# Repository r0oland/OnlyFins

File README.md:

# OnlyFins

ESPHome based smart radiator fans with temperature guided PWM Fan control. 

Ìnstall uv:
`winget install uv`

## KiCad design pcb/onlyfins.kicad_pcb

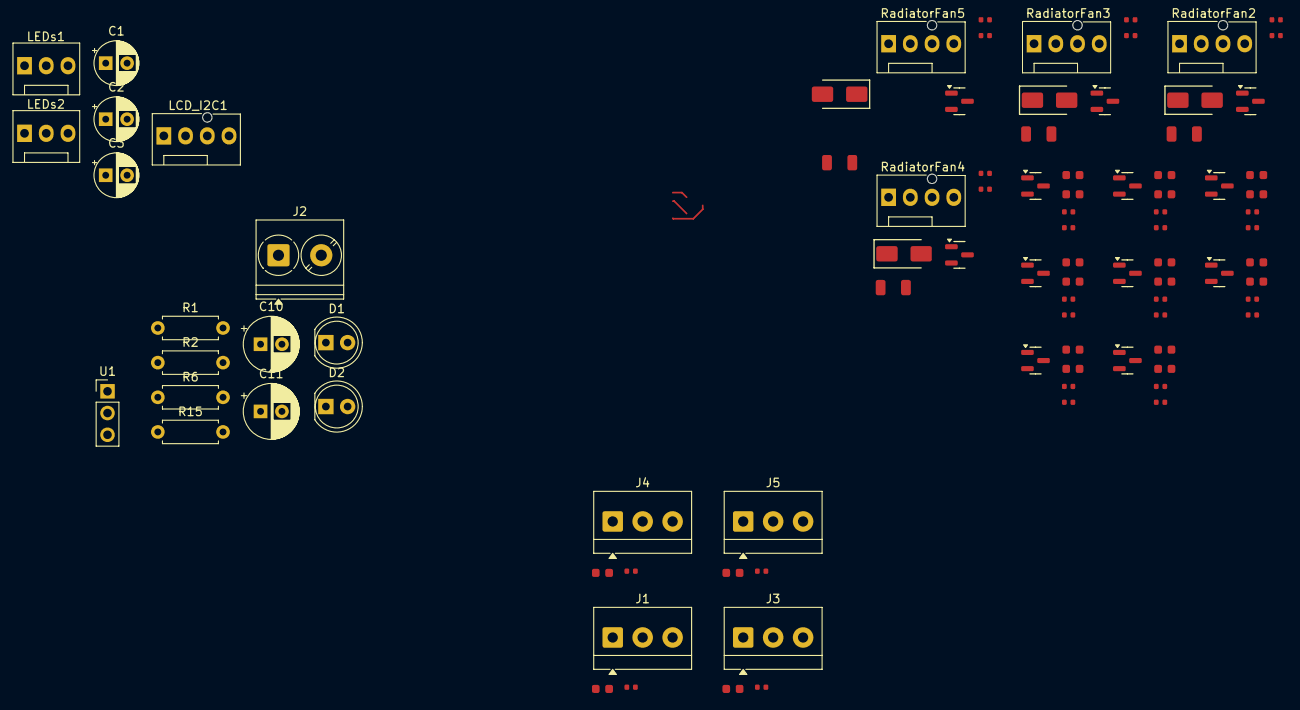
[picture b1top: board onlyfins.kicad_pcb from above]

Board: 2 copper layers, 92 parts (0 on the bottom side), 52 nets.

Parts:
C1, C2, C3: 22u; CP_Radial_D5.0mm_P2.50mm
C6, C7, C8, C9, C12, C13, C14, C15, C16, C17, C18, C19, C20, C21, C22, C23, C28, C29, C30, C31: 100nF; C_0603
C10, C11: 100u; CP_Radial_D6.3mm_P2.50mm
C24, C25, C26, C27: 22uF; C_1206
D1: 5V; LED_D5.0mm
D2: 12V; LED_D5.0mm
D6, D7, D8, D9: SS14; D_SMA
J1, J3, J4, J5: Temp1; TerminalBlock_4Ucon_1x03_P3.50mm_Horizontal
J2: 12V_in; TerminalBlock_Phoenix_PT-1,5-2-5.0-H_1x02_P5.00mm_Horizontal
LCD_I2C1: LCD_I2C; FanPinHeader_1x04_P2.54mm_Vertical
LEDs1, LEDs2: DigiTempSens1; FanPinHeader_1x03_P2.54mm_Vertical
Q1, Q3, Q5, Q6, Q8, Q9, Q11, Q12: BSS138; Q_SOT-23
Q2, Q4, Q7, Q10: AO3400A; Q_SOT-23
R1, R6, R15: 300; R_Axial_DIN0207_L6.3mm_D2.5mm_P7.62mm_Horizontal
R2: 1k; R_Axial_DIN0207_L6.3mm_D2.5mm_P7.62mm_Horizontal
R4, R5, R17, R19, R20, R22, R23, R24, R25, R26, R28, R29, R30, R31, R32, R34, R35, R36, R37, R38: 10kΩ; R_0402
R7, R8, R9, R10: 4.7kΩ; R_0402
R18, R21, R27, R33: 1kΩ; R_0402
RadiatorFan2, RadiatorFan3, RadiatorFan4, RadiatorFan5: Fan_4pin; FanPinHeader_1x04_P2.54mm_Vertical
U1: L7805; PinHeader_1x03_P2.54mm_Vertical

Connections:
+3V3: C1.1, C28.1, C29.1, C30.1, C31.1, J1.1, J3.1, J4.1, J5.1, LCD_I2C1.4, R7.1, R8.1, R9.1, R10.1
+5V: C2.1, R1.2, U1.3 (OUT)
+12V: C3.1, C10.1, C11.1, C24.1, C25.1, C26.1, C27.1, D6.1, D7.1, D8.1, D9.1, J2.1, LEDs1.3, LEDs2.3, R2.2, RadiatorFan2.2 (+), RadiatorFan3.2 (+), RadiatorFan4.2 (+), RadiatorFan5.2 (+), U1.1 (IN)
/Fan 1/level_shifter1/sig_hv: C7.2, Q3.3 (D), R20.2
/Fan 1/level_shifter1/sig_lv: C17.2, Q3.2 (S), R19.2
/Fan 1/level_shifter1/vcc_hv: C7.1, R20.1
/Fan 1/level_shifter1/vcc_lv: Q3.1 (G), R19.1
/Fan 1/level_shifter/sig_hv: C6.2, Q1.3 (D), R5.2
/Fan 1/level_shifter/sig_lv: C16.2, Q1.2 (S), R4.2
/Fan 1/level_shifter/vcc_hv: C6.1, R5.1
/Fan 1/level_shifter/vcc_lv: Q1.1 (G), R4.1
/Fan 2/level_shifter1/sig_hv: C9.2, Q6.3 (D), R26.2
/Fan 2/level_shifter1/sig_lv: C19.2, Q6.2 (S), R25.2
/Fan 2/level_shifter1/vcc_hv: C9.1, R26.1
/Fan 2/level_shifter1/vcc_lv: Q6.1 (G), R25.1
/Fan 2/level_shifter/sig_hv: C8.2, Q5.3 (D), R24.2
/Fan 2/level_shifter/sig_lv: C18.2, Q5.2 (S), R23.2
/Fan 2/level_shifter/vcc_hv: C8.1, R24.1
/Fan 2/level_shifter/vcc_lv: Q5.1 (G), R23.1
/Fan 3/level_shifter1/sig_hv: C13.2, Q9.3 (D), R32.2
/Fan 3/level_shifter1/sig_lv: C21.2, Q9.2 (S), R31.2
/Fan 3/level_shifter1/vcc_hv: C13.1, R32.1
/Fan 3/level_shifter1/vcc_lv: Q9.1 (G), R31.1
/Fan 3/level_shifter/sig_hv: C12.2, Q8.3 (D), R30.2
/Fan 3/level_shifter/sig_lv: C20.2, Q8.2 (S), R29.2
/Fan 3/level_shifter/vcc_hv: C12.1, R30.1
/Fan 3/level_shifter/vcc_lv: Q8.1 (G), R29.1
/Fan 4/level_shifter1/sig_hv: C15.2, Q12.3 (D), R38.2
/Fan 4/level_shifter1/sig_lv: C23.2, Q12.2 (S), R37.2
/Fan 4/level_shifter1/vcc_hv: C15.1, R38.1
/Fan 4/level_shifter1/vcc_lv: Q12.1 (G), R37.1
/Fan 4/level_shifter/sig_hv: C14.2, Q11.3 (D), R36.2
/Fan 4/level_shifter/sig_lv: C22.2, Q11.2 (S), R35.2
/Fan 4/level_shifter/vcc_hv: C14.1, R36.1
/Fan 4/level_shifter/vcc_lv: Q11.1 (G), R35.1
/Temp1/data: J1.2, R7.2
/Temp2/data: J3.2, R8.2
/Temp3/data: J4.2, R9.2
/Temp4/data: J5.2, R10.2
GND: C1.2, C2.2, C3.2, C10.2, C11.2, C28.2, C29.2, C30.2, C31.2, D1.1 (K), D2.1 (K), J1.3, J2.2, J3.3, J4.3, J5.3, LCD_I2C1.1, LEDs1.1, LEDs2.1, Q2.2 (S), Q4.2 (S), Q7.2 (S), Q10.2 (S), R17.2, R22.2, R28.2, R34.2, U1.2 (GND)
unnamed: D1.2 (A), R1.1
unnamed: D2.2 (A), R2.1
unnamed: LEDs1.2, R15.2
unnamed: LEDs2.2, R6.2
unnamed: C24.2, D6.2, Q2.3 (D), RadiatorFan2.1 (-)
unnamed: Q2.1 (G), R17.1, R18.2
unnamed: C25.2, D7.2, Q4.3 (D), RadiatorFan3.1 (-)
unnamed: Q4.1 (G), R21.2, R22.1
unnamed: C26.2, D8.2, Q7.3 (D), RadiatorFan4.1 (-)
unnamed: Q7.1 (G), R27.2, R28.1
unnamed: C27.2, D9.2, Q10.3 (D), RadiatorFan5.1 (-)
unnamed: Q10.1 (G), R33.2, R34.1

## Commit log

2026-01-31 Add submodules configuration
2026-01-31 Add secrets submodule
2026-01-31 Init with pretotype working, hardware files missing
2026-01-31 Starting KiCad desing based on older project
2026-02-01 Adding subsheets for fan control
2026-02-03 Add temperature sensors
